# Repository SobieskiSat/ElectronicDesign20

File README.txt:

View this project on [CADLAB.io](https://cadlab.io/project/2295). 

Electronic design of the mainboard. more details TBA.

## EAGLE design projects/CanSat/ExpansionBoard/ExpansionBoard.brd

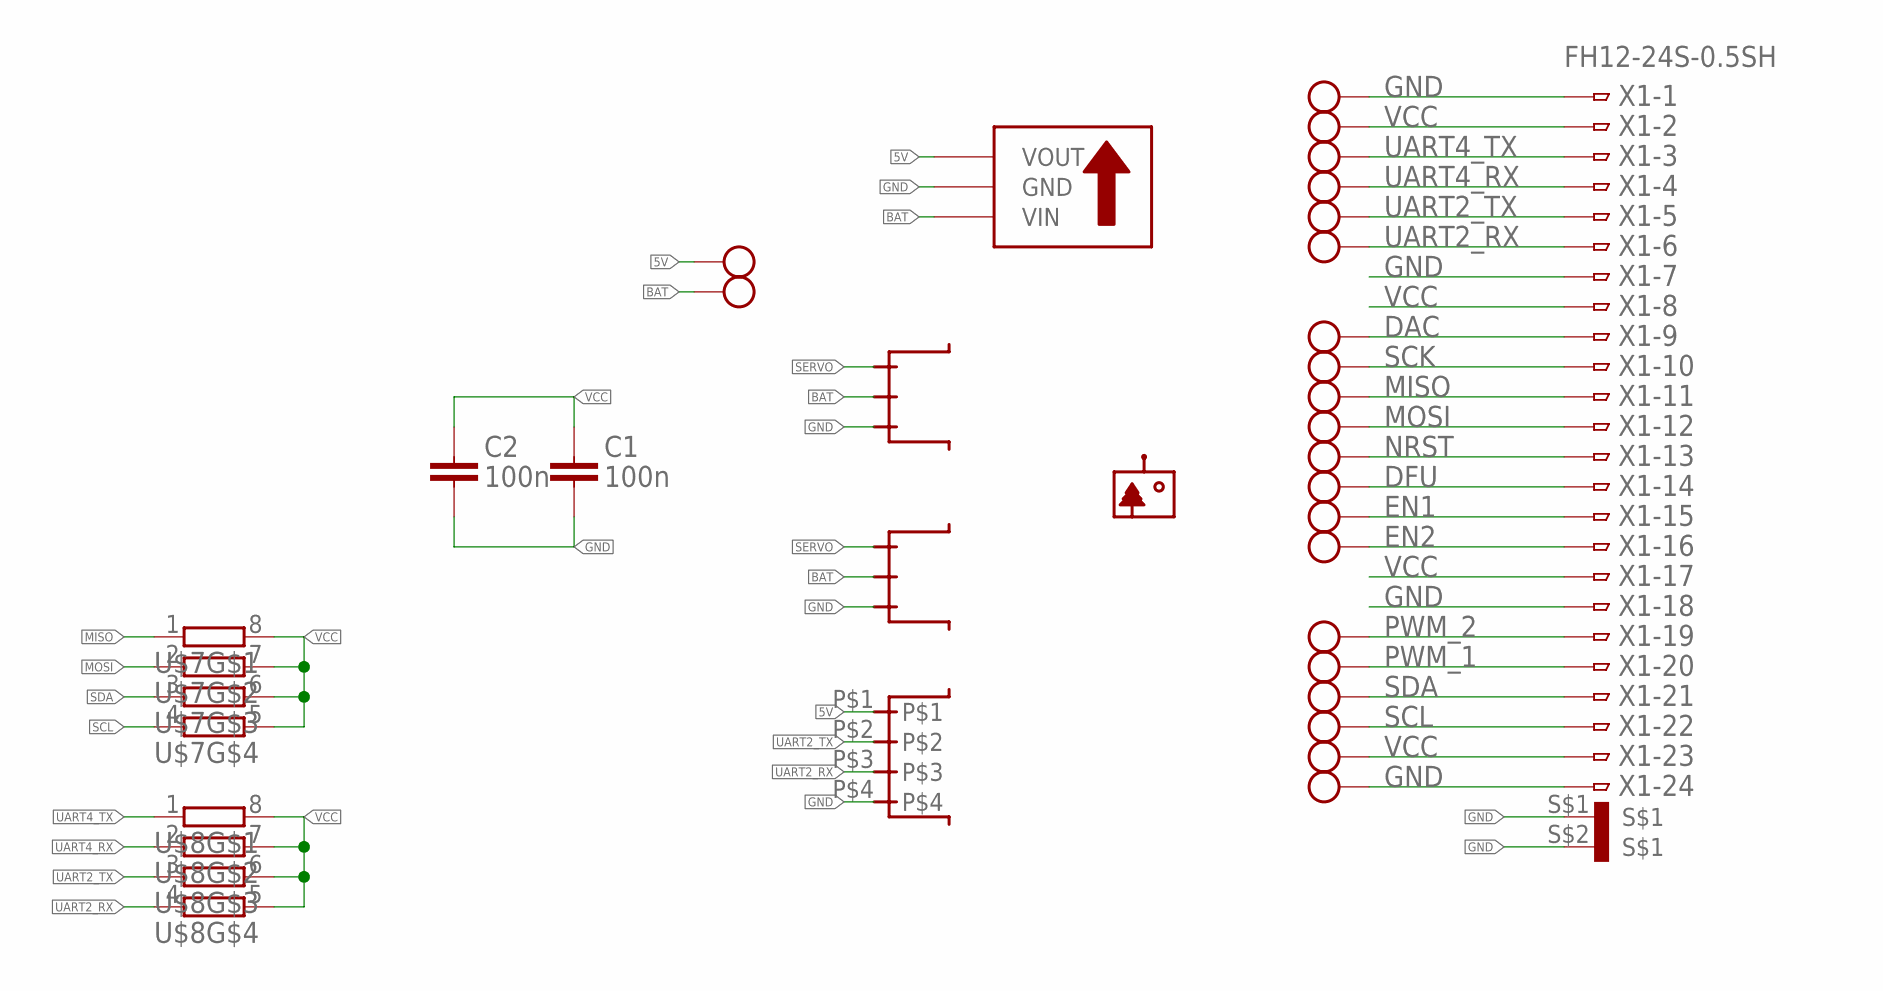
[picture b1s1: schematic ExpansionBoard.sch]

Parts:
C1, C2: 100n; C0603
U$1, U$23: THT_PADSQ; THT_PAD_SQ
U$2, U$3, U$4, U$5, U$6, U$9, U$10, U$11, U$12, U$13, U$14, U$15, U$16, U$19, U$20, U$21, U$22, U$24, U$27, U$30: THT_PAD
U$7, U$8: RESISTORARRAY; 0603-ARC
U$17: LOGOSQSM
U$25: MODULE_STEPUP
U$26: CONNECTOR_F_X4_JST_SMD; 4X_JSTSMD_F
U$28, U$29: CONNECTOR_F_X3_JST_SMD; 3X_JSTSMD_F
X1: FH12-24S-0.5SH

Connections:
5V: U$25.VOUT, U$26.P$1, U$27.P$1
BAT: U$25.VIN, U$28.P$2, U$29.P$2, U$30.P$1
DAC: U$9.P$1, X1.9 (1)
DFU: U$14.P$1, X1.14 (1)
EN1: U$15.P$1, X1.15 (1)
EN2: U$16.P$1, X1.16 (1)
GND: C1.2, C2.2, U$1.P$1, U$23.P$1, U$25.GND, U$26.P$4, U$28.P$3, U$29.P$3, X1.1, X1.7 (1), X1.18 (1), X1.24 (1), X1.S$1, X1.S$2
MISO: U$7.1, U$11.P$1, X1.11 (1)
MOSI: U$7.2 (1), U$12.P$1, X1.12 (1)
NRST: U$13.P$1, X1.13 (1)
PWM_1: U$20.P$1, X1.20 (1)
PWM_2: U$19.P$1, X1.19 (1)
SCK: U$10.P$1, X1.10 (1)
SCL: U$7.4 (1), U$22.P$1, X1.22 (1)
SDA: U$7.3 (1), U$21.P$1, X1.21 (1)
SERVO: U$28.P$1, U$29.P$1
UART2_RX: U$6.P$1, U$8.4 (1), U$26.P$3, X1.6 (1)
UART2_TX: U$5.P$1, U$8.3 (1), U$26.P$2, X1.5 (1)
UART4_RX: U$4.P$1, U$8.2 (1), X1.4 (1)
UART4_TX: U$3.P$1, U$8.1, X1.3 (1)
VCC: C1.1, C2.1, U$2.P$1, U$7.5 (2), U$7.6 (2), U$7.7 (2), U$7.8 (2), U$8.5 (2), U$8.6 (2), U$8.7 (2), U$8.8 (2), U$24.P$1, X1.2 (1), X1.8 (1), X1.17 (1), X1.23 (1)

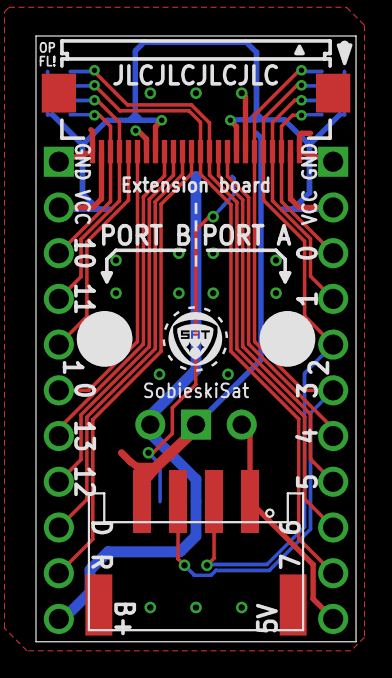
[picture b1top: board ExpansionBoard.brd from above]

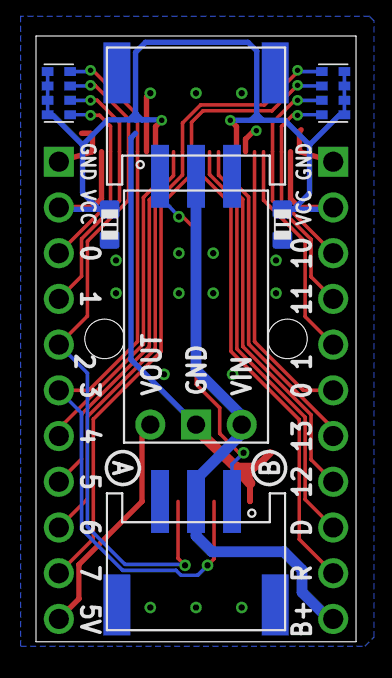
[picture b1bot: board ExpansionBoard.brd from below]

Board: 2 copper layers, 17.8 x 33.7 mm, 32 parts (7 on the bottom side), 21 nets.

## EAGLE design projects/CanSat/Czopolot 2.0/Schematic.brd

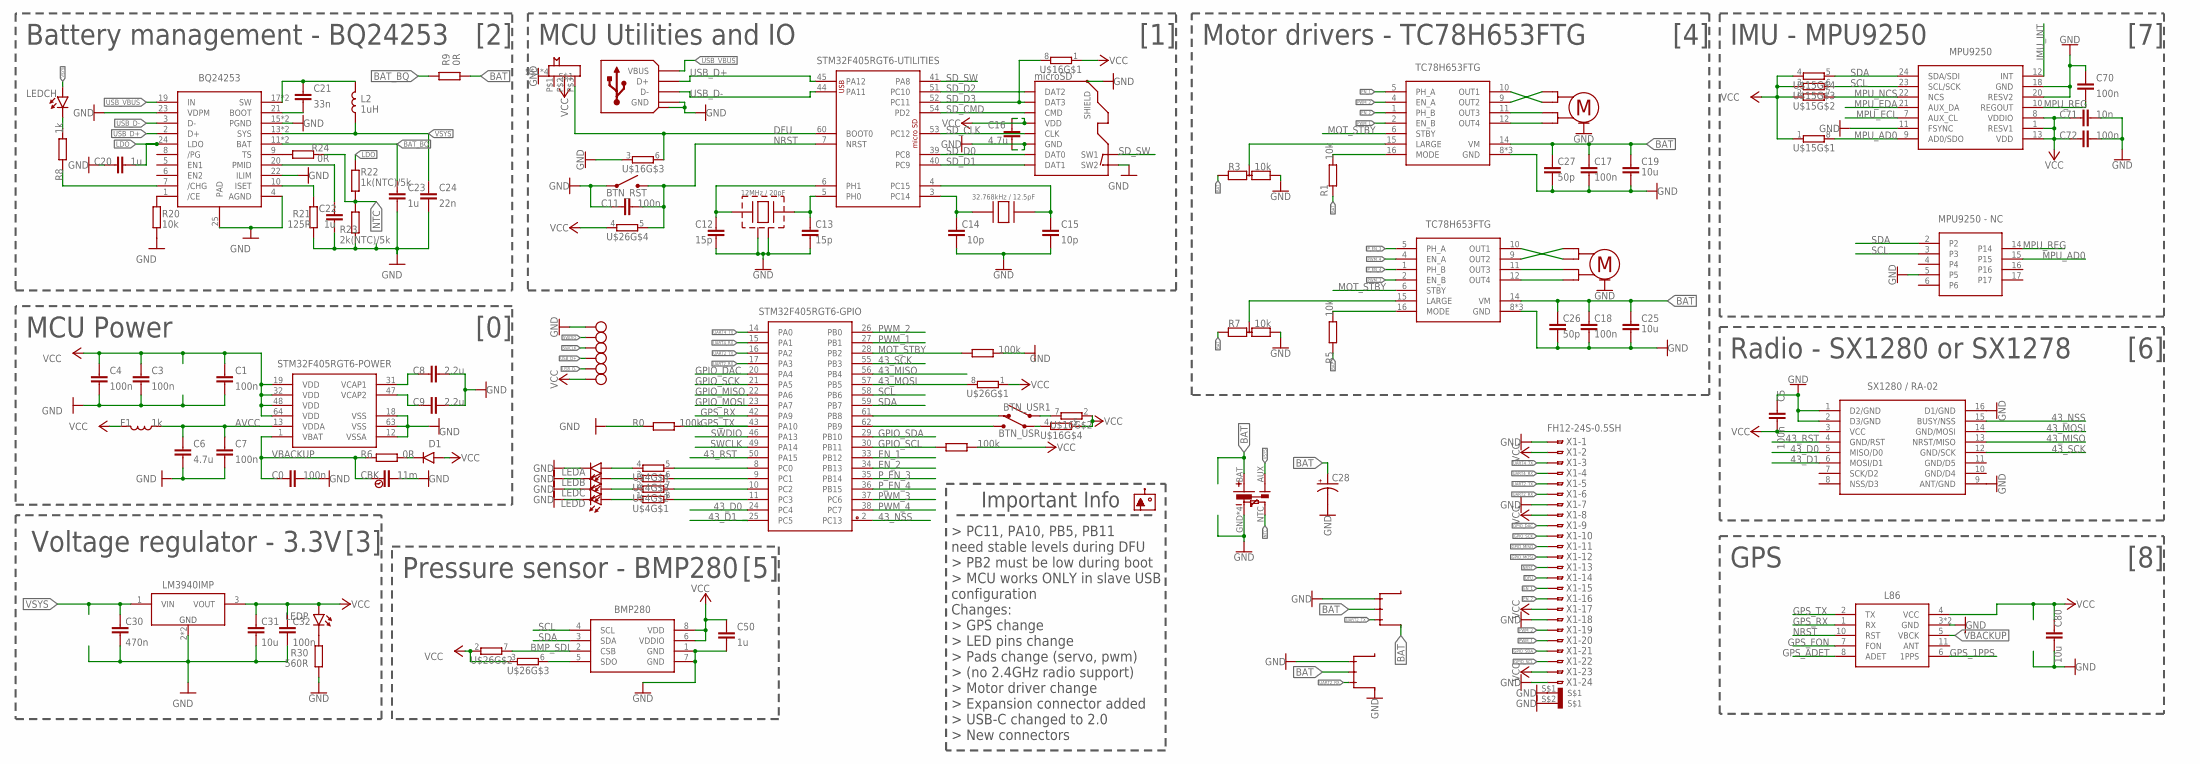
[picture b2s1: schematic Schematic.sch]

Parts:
BTN_DFU: SLIDE-SWITCH2; SLIDE-SWITCH-2
BTN_RST: PUSH-SWITCH; SWITCH_SMD
BTN_USR, BTN_USR1: PUSH-SWITCH; SWITCH_SMD
C0, C1, C3, C4, C5, C7, C11, C17, C18, C32, C70, C72: 100n; C0603
C6, C16: 4.7u; C0603
C8, C9: 2.2u; C0603
C12, C13: 15p; C0603
C14, C15: 10p; C0603
C19, C25, C31: 10u; C1206
C20, C22, C23, C50: 1u; C0603
C21: 33n; C0603
C24: 22n; C0603
C26, C27: 50p; C0603
C28: CPOL-US153CLV-0405; 153CLV-0405
C30: 470n; C0603
C71: 10n; C0603
C80: 10u; C0603
CBK: 11m; CPH3225A
D1: DIODE; R0603
F1: 1k; R0603
L2: 1uH; INDUCTOR_VISHAY
LEDA: LED0805; CHIPLED_0805
LEDB: LED0805; CHIPLED_0805
LEDC: LED0805; CHIPLED_0805
LEDCH: LED0805; CHIPLED_0805
LEDD: LED0805; CHIPLED_0805
LEDP: LED0805; CHIPLED_0805
LM3940IMP: REGULATOR; SOT230P700X180-4N
R0, R2, R4: 100k; R0603
R1, R5, R20: 10k; R0603
R3, R7: 10k; DR0603
R6, R9, R24: 0R; R0603
R8: 1k; R0603
R21: 125R; R0603
R22: 1k(NTC)/5k; R0603
R23: 2k(NTC)/5k; R0603
R30: 560R; R0603
U$1: STM32F405RGT6; QFP50P1200X1200X160-64N
U$2: MICROSD_HOLDER
U$3: L86
U$4, U$15, U$16, U$26: RESISTORARRAY; 0603-ARC
U$5: 32.768kHz / 12.5pF; OSC32X15
U$6: 12MHz / 20pF; OSCCC320X250X80N
U$7: USB2.0; USB-C(2)
U$8: BMP280
U$9: MPU9250USR; MPU9250
U$10: BQ24253; QFN50P400X400X100-25T270N
U$11, U$12: TC78H653FTG; QFN50P300X300X90-17T170N
U$13, U$17: MOTOR_DUO; 4(2)X_JSTSMD_F
U$14: BAT_JST_4(3); 4(3)X_JSTSMD_F
U$18: LOGOSQSM
U$19, U$20: CONNECTOR_F_X3_JST_SMD; 3X_JSTSMD_F
U$21: LORADUO; MODULE_SX1280
U$25: GPIO_DEBUG
X1: FH12-24S-0.5SH

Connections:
43_D0: U$1.24 (PC4), U$21.5 (MISO/D0)
43_D1: U$1.25 (PC5), U$21.6 (MOSI/D1)
43_MISO: U$1.56 (PB4), U$21.13 (NRST/MISO)
43_MOSI: U$1.57 (PB5), U$21.14 (GND/MOSI), U$26.8 (2)
43_NSS: U$1.2 (PC13), U$21.15 (BUSY/NSS)
43_RST: U$1.50 (PA15), U$21.4 (GND/RST)
43_SCK: U$1.55 (PB3), U$21.12 (GND/SCK)
AVCC: C6.1, C7.1, F1.2, U$1.13 (VDDA)
BAT: C17.1, C18.1, C19.1, C25.1, C26.1, C27.1, C28.+, R1.1, R3.2, R5.1, R7.2, R9.1, U$11.14 (VM), U$12.14 (VM), U$14.BAT (+), U$19.P$2, U$19.S$1, U$19.S$2, U$20.P$2
BAT_BQ: C23.1, R9.2, U$10.11 (BAT), U$10.12 (BAT)
BMP_SDI: U$8.2 (CSB), U$26.7 (2)
BMP_SDO: U$8.5 (SDO), U$26.6 (2)
DFU: BTN_DFU.P$3, U$1.60 (BOOT0), U$16.6 (2), X1.14 (1)
EN_1: U$1.33 (PB12), U$12.5 (PH_A), X1.15 (1)
EN_2: U$1.34 (PB13), U$12.1 (PH_B), X1.16 (1)
GND: BTN_DFU.S$1, BTN_DFU.S$2, BTN_DFU.S$3, BTN_DFU.S$4, BTN_RST.P$1, BTN_RST.P$4, C0.2, C1.2, C3.2, C4.2, C5.1, C6.2, C7.2, C8.2, C9.2, C11.1, C12.2, C13.2, C14.2, C15.2, C16.1, C17.2, C18.2, C19.2, C20.1, C22.2, C23.2, C24.2, C25.2, C26.2, C27.2, C28.-, C30.2, C31.2, C32.2, C50.2, C70.1, C71.2, C72.2, C80.2, CBK.P$2 (2), LEDA.C, LEDB.C, LEDC.C, LEDD.C, LM3940IMP.2 (GND), LM3940IMP.4 (GND), R0.1, R2.1, R3.3, R7.3, R20.1, R21.1, R23.1, R30.2, U$1.12 (VSSA), U$1.18 (VSS), U$1.63 (VSS), U$2.GND, U$2.SHIELD@1 (SHIELD), U$2.SHIELD@2 (SHIELD), U$2.SHIELD@3 (SHIELD), U$2.SHIELD@4 (SHIELD), U$2.SW2, U$3.3 (GND), U$3.12 (GND), U$6.2 (GND), U$6.4 (GND), U$7.A1 (GND), U$7.A12 (GND), U$7.B1 (GND), U$7.B12 (GND), U$7.MID@1 (SHIELD), U$7.MID@2 (SHIELD), U$7.S$1 (GND), U$7.S$2 (GND), U$7.S$3 (GND), U$7.S$4 (GND), U$7.S$5 (GND), U$7.S$6 (GND), U$7.S$7 (GND), U$7.S$8 (GND), U$8.1 (GND), U$8.7 (GND), U$9.5, U$9.11 (FSYNC), U$9.18 (GND), U$9.20 (RESV2), U$10.4 (AGND), U$10.15 (PGND), U$10.16 (PGND), U$10.22 (ILIM), U$10.23 (VDPM), U$10.25 (PAD), U$11.8 (GND), U$11.13 (GND), U$11.17 (GND), U$12.8 (GND), U$12.13 (GND), U$12.17 (GND), U$13.S$1, U$13.S$2, U$13.S$3, U$13.S$4, U$14.GND (-), U$14.S$1 (-), U$14.S$2 (-), U$14.S$3 (-), U$16.3 (1), U$17.S$1, U$17.S$2, U$17.S$3, U$17.S$4, U$19.P$1, U$20.P$1, U$20.S$1, U$20.S$2, U$21.1 (D2/GND), U$21.2 (D3/GND), U$21.9 (ANT/GND), U$21.16 (D1/GND), U$25.P$1, X1.1, X1.7 (1), X1.18 (1), X1.24 (1), X1.S$1, X1.S$2
GPIO_DAC: U$1.20 (PA4), X1.9 (1)
GPIO_MISO: U$1.22 (PA6), X1.11 (1)
GPIO_MOSI: U$1.23 (PA7), X1.12 (1)
GPIO_SCK: U$1.21 (PA5), X1.10 (1)
GPIO_SCL: R4.2, U$1.30 (PB11), X1.22 (1)
GPIO_SDA: U$1.29 (PB10), X1.21 (1)
GPS_1PPS: U$3.6 (1PPS)
GPS_ADET: U$3.8 (ADET)
GPS_FON: U$3.7 (FON)
GPS_RX: U$1.42 (PA9), U$3.1 (RX)
GPS_TX: R0.2, U$1.43 (PA10), U$3.2 (TX)
IMU_INT: U$9.12 (INT)
LDO: C20.2, R22.2, U$10.24 (LDO)
MOT_STBY: R2.2, U$1.28 (PB2), U$11.6 (STBY), U$12.6 (STBY)
MPU_AD0: U$9.9 (AD0/SDO), U$9.15, U$15.8 (2)
MPU_ECL: U$9.7 (AUX_CL)
MPU_EDA: U$9.21 (AUX_DA)
MPU_NCS: U$9.22 (NCS), U$15.7 (2)
MPU_REG: C70.2, U$9.10 (REGOUT), U$9.14
unnamed: LEDD.A, U$4.1
unnamed: LEDC.A, U$4.2 (1)
unnamed: LEDCH.C, R8.2
unnamed: U$11.9 (OUT2), U$13.P$1
unnamed: BTN_USR.P$2, BTN_USR.P$3, U$1.62 (PB9)
unnamed: C21.2, U$10.21 (BOOT)
unnamed: BTN_USR.P$1, BTN_USR.P$4, U$16.4 (1)
unnamed: C9.1, U$1.47 (VCAP2)
unnamed: C8.1, U$1.31 (VCAP1)
unnamed: R8.1, U$10.7 (/CHG)
unnamed: C12.1, U$1.6 (PH1), U$6.1
unnamed: C13.1, U$1.5 (PH0), U$6.3
unnamed: C14.1, U$1.3 (PC14), U$5.P$1
unnamed: C15.1, U$1.4 (PC15), U$5.P$2
unnamed: U$1.8 (PC0), U$4.5 (2)
unnamed: R24.2, U$10.9 (TS)
unnamed: R21.2, U$10.10 (ISET)
unnamed: U$1.11 (PC3), U$4.8 (2)
unnamed: U$1.10 (PC2), U$4.7 (2)
unnamed: C21.1, L2.P$1, U$10.17 (SW), U$10.18 (SW)
unnamed: LEDP.C, R30.1
unnamed: U$11.10 (OUT1), U$13.P$2
unnamed: C22.1, U$10.20 (PMID)
unnamed: BTN_USR1.P$1, BTN_USR1.P$4, U$16.7 (2)
unnamed: U$1.9 (PC1), U$4.6 (2)
unnamed: R20.2, U$10.1 (/CE)
unnamed: BTN_USR1.P$2, BTN_USR1.P$3, U$1.61 (PB8)
unnamed: U$11.11 (OUT3), U$13.P$3
unnamed: U$11.12 (OUT4), U$13.P$4
unnamed: U$12.9 (OUT2), U$17.P$1
unnamed: U$12.10 (OUT1), U$17.P$2
unnamed: U$12.11 (OUT3), U$17.P$3
unnamed: U$12.12 (OUT4), U$17.P$4
unnamed: R1.2, U$12.16 (MODE)
unnamed: LEDB.A, U$4.3 (1)
unnamed: LEDA.A, U$4.4 (1)
unnamed: R3.1, U$12.15 (LARGE)
unnamed: R5.2, U$11.16 (MODE)
unnamed: D1.2, R6.2
unnamed: R7.1, U$11.15 (LARGE)
NRST: BTN_RST.P$2, BTN_RST.P$3, C11.2, U$1.7 (NRST), U$3.10 (RST), U$26.5 (2), X1.13 (1)
NTC: R22.1, R23.2, R24.1, U$14.NTC
PWM_1: U$1.27 (PB1), U$12.2 (EN_B), X1.20 (1)
PWM_2: U$1.26 (PB0), U$12.4 (EN_A), X1.19 (1)
PWM_3: U$1.37 (PC6), U$11.2 (EN_B)
PWM_4: U$1.38 (PC7), U$11.4 (EN_A)
P_EN_3: U$1.35 (PB14), U$11.5 (PH_A)
P_EN_4: U$1.36 (PB15), U$11.1 (PH_B)
SCL: U$1.58 (PB6), U$8.4 (SCL), U$9.3, U$9.23 (SCL/SCK), U$15.6 (2)
SDA: U$1.59 (PB7), U$8.3 (SDA), U$9.2, U$9.24 (SDA/SDI), U$15.5 (2)
SD_CLK: U$1.53 (PC12), U$2.CLK
SD_CMD: U$1.54 (PD2), U$2.CMD
SD_D0: U$1.39 (PC8), U$2.D0 (DAT0)
SD_D1: U$1.40 (PC9), U$2.D1 (DAT1)
SD_D2: U$1.51 (PC10), U$2.D2 (DAT2)
SD_D3: U$1.52 (PC11), U$2.D3 (DAT3), U$16.8 (2)
SD_SW: U$1.41 (PA8), U$2.SW1
SWCLK: U$1.49 (PA14), U$25.P$3
SWDIO: U$1.46 (PA13), U$25.P$2
UART2_RX: U$1.17 (PA3), U$20.P$3, X1.6 (1)
UART2_TX: U$1.16 (PA2), U$19.P$3, X1.5 (1)
UART4_RX: U$1.15 (PA1), X1.4 (1)
UART4_TX: U$1.14 (PA0), X1.3 (1)
USB_D+: U$1.45 (PA12), U$7.A6 (D+), U$7.B6 (D+), U$10.2 (D+), U$25.P$4
USB_D-: U$1.44 (PA11), U$7.A7 (D-), U$7.B7 (D-), U$10.3 (D-), U$25.P$5
USB_VBUS: U$7.A4 (VBUS), U$7.A9 (VBUS), U$7.B4 (VBUS), U$7.B9 (VBUS), U$10.19 (IN)
VBACKUP: C0.1, CBK.P$1 (1), R6.1, U$1.1 (VBAT), U$3.5 (VBCK)
VCC: BTN_DFU.P$2, C1.1, C3.1, C4.1, C5.2, C16.2, C31.1, C32.1, C50.1, C71.1, C72.1, C80.1, D1.1, F1.1, LEDP.A, LM3940IMP.3 (VOUT), R4.1, U$1.19 (VDD), U$1.32 (VDD), U$1.48 (VDD), U$1.64 (VDD), U$2.VCC (VDD), U$3.4 (VCC), U$8.6 (VDDIO), U$8.8 (VDD), U$9.1 (RESV1), U$9.8 (VDDIO), U$9.13 (VDD), U$15.1, U$15.2 (1), U$15.3 (1), U$15.4 (1), U$16.1, U$16.2 (1), U$16.5 (2), U$21.3 (VCC), U$25.P$6, U$26.1, U$26.2 (1), U$26.3 (1), U$26.4 (1), X1.2 (1), X1.8 (1), X1.17 (1), X1.23 (1)
VSYS: C24.1, C30.1, L2.P$2, LEDCH.A, LM3940IMP.1 (VIN), U$10.13 (SYS), U$10.14 (SYS), U$14.AUX (AUX+)

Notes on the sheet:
GPS
Pressure sensor - BMP280
IMU - MPU9250
Radio - SX1280 or SX1278
Battery management - BQ24253
Voltage regulator - 3.3V
MCU Power
MCU Utilities and IO
Important Info
Motor drivers - TC78H653FTG
[0]
[1]
[2]
[3]
[4]
[5]
[6]
[7]
[8]
Changes: > GPS change > LED pins change > Pads change (servo, pwm) > (no 2.4GHz radio support) > Motor driver change > Expansion connector added > USB-C changed to 2.0 > New connectors

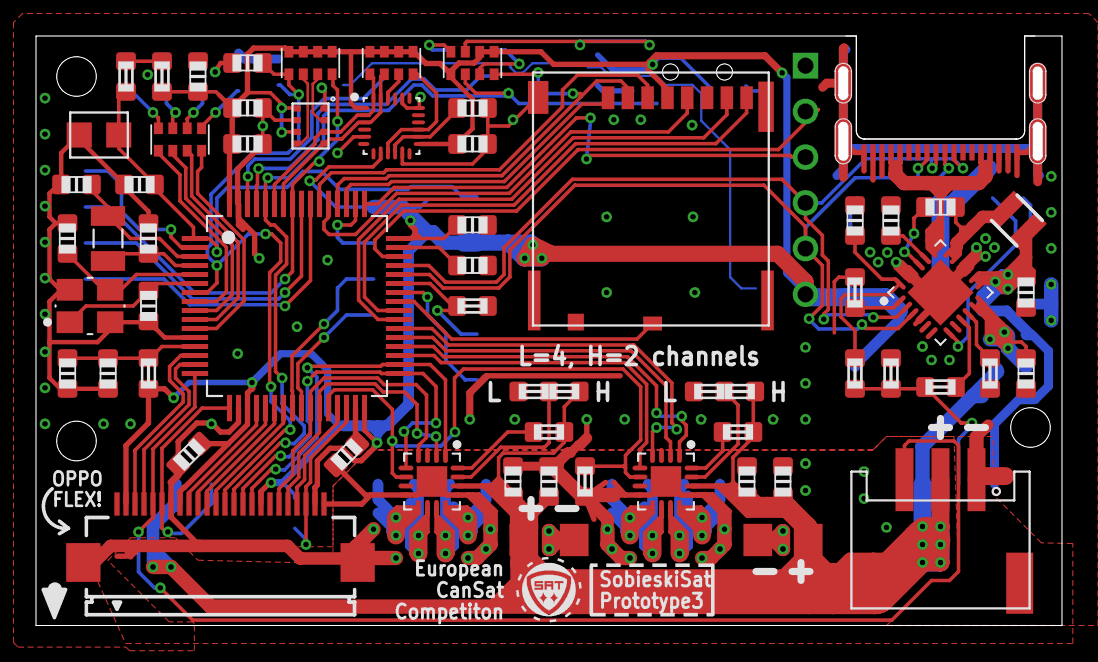
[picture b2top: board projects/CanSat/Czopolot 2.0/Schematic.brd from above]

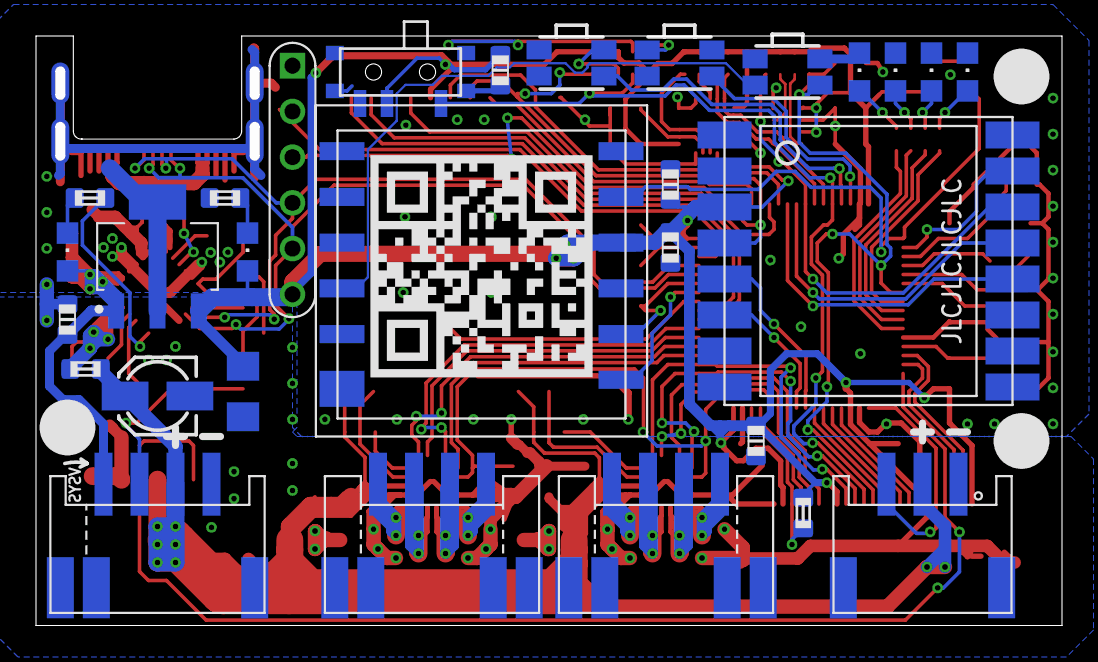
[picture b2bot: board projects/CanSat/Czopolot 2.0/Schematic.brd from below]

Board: 2 copper layers, 57.0 x 32.8 mm, 90 parts (29 on the bottom side), 98 nets.

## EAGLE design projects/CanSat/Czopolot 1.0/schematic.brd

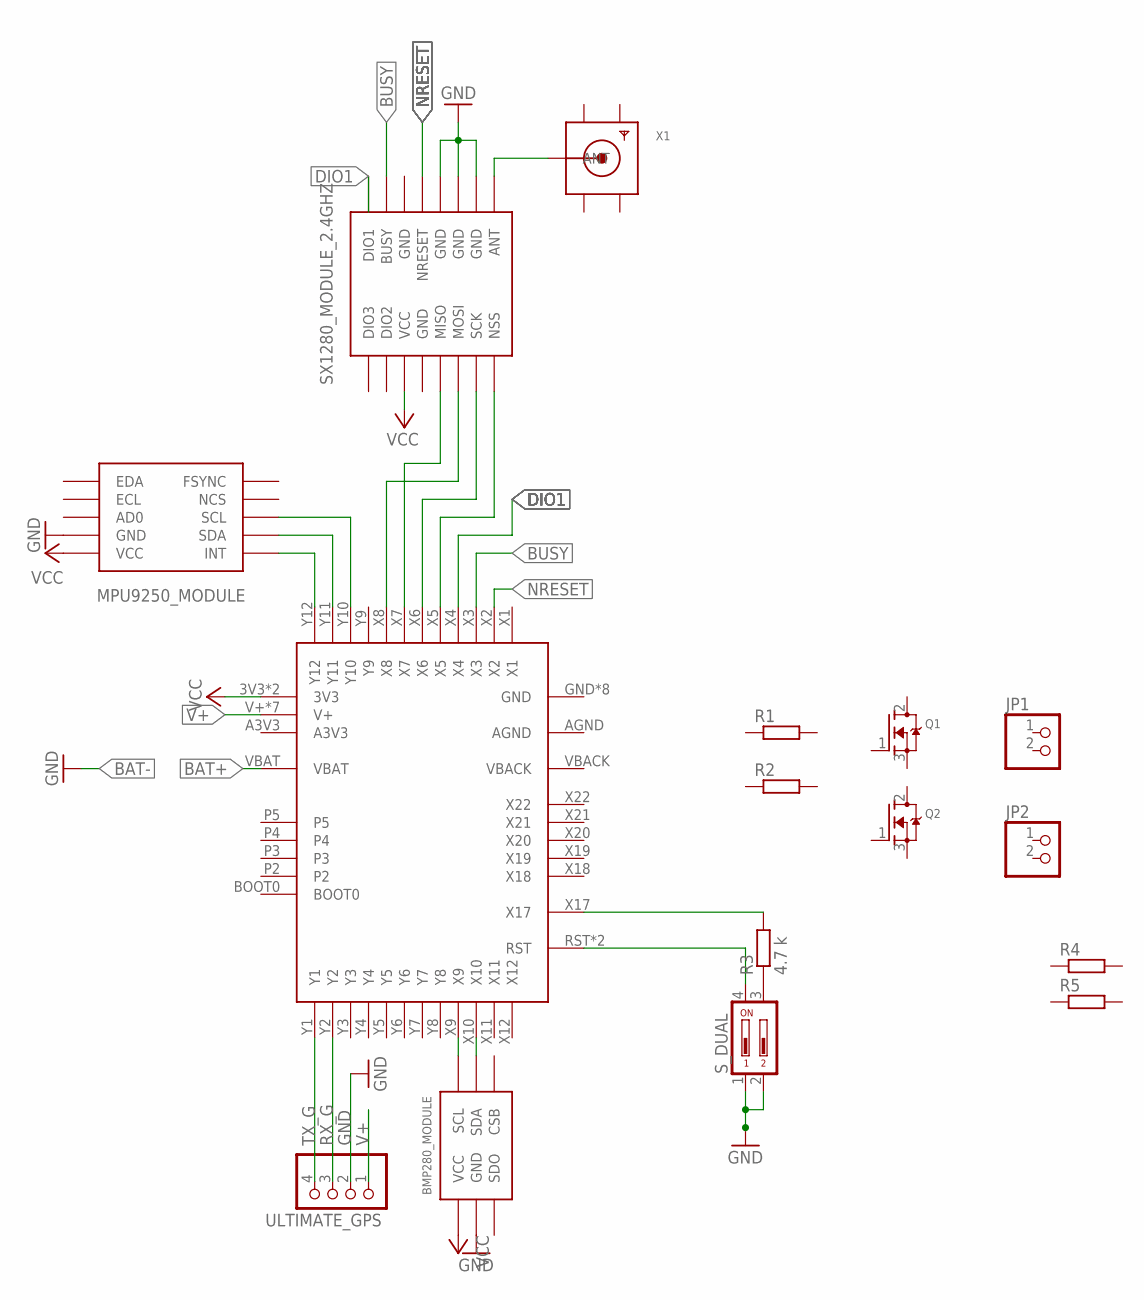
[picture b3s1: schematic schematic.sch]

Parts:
JP1, JP2: PINHD-1X2; 1X02
Q1, Q2: MOSFET-NGDS_TO220V; TO220V
R1, R2, R4: R-EU_0204/7; 0204/7
R3: 4.7 k; 0204/7
R5: R-EU_0207/10; 0207/10
U$1: PYBOARD1.1; MODULE_PYBOARD
U$3: MPU9250; MODULE_MPU9250
U$4: BMP280; MODULE_BMP280
U$5: SWITCH_DUAL
U$6: SX1280_2.4GHZ; MODULE_SX1280_THT
ULTIMATE_GPS: PINHD-1X4; 1X04
X1: SMACONNECTOR; SMA_DIP

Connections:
BAT+: U$1.VBAT
BUSY: U$1.X3, U$6.BUSY
DIO1: U$1.X4
GND: U$3.GND, U$4.GND, U$5.1, U$5.2, U$6.GND@3 (GND), U$6.GND@4 (GND), U$6.GND@5 (GND), ULTIMATE_GPS.2
GND1: X1.GND1
GND2: X1.GND2
GND3: X1.GND3
GND4: X1.GND4
unnamed: U$1.X5, U$6.NSS
unnamed: U$1.X6, U$6.SCK
unnamed: U$1.X8, U$6.MOSI
unnamed: U$1.X7, U$6.MISO
unnamed: U$6.ANT, X1.ANTENNA (ANT)
unnamed: R3.1, U$5.3
unnamed: U$1.Y11, U$3.SDA
unnamed: U$1.Y10, U$3.SCL
unnamed: U$1.Y12, U$3.INT
unnamed: U$1.X9, U$4.SCL
unnamed: U$1.X10, U$4.SDA
unnamed: U$1.RST, U$1.RST1 (RST), U$5.4
unnamed: R3.2, U$1.X17
NRESET: U$1.X2, U$6.NRESET
RX_G: U$1.Y2, ULTIMATE_GPS.3
TX_G: U$1.Y1, ULTIMATE_GPS.4
V+: U$1.V+, U$1.V+1 (V+), U$1.V+2 (V+), U$1.V+3 (V+), U$1.V+4 (V+), U$1.V+5 (V+), U$1.V+6 (V+), ULTIMATE_GPS.1
VCC: U$1.3V3, U$1.3V3-1 (3V3), U$3.VCC, U$4.VCC, U$6.VCC

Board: 2 copper layers, 16 parts (0 on the bottom side), 20 nets, no tracks yet.

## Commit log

2019-11-17 Backlink to CADLAB.io has been added.
2019-11-18 File upload
2019-11-18 File separation
2019-11-18 null
2019-11-18 Add README.txt
2019-11-18 File update
2019-11-25 Work work..
2019-11-26 Work work...
2019-12-01 Work work.....
2019-12-04 updatejs
    pyboard
2019-12-04 Gitignore update
2019-12-05 Routing & placing ver.1
    Proposed routing for board.
    > Everyting seems optimal so far except for:
    > BMP280 (?move to the right)
2019-12-07 Schrinking...
2019-12-08 Oh God that's small..
2019-12-09 USB-C update
2019-12-09 Updated USB-C
2019-12-09 Backup upload
2019-12-09 usb-c fix
2019-12-09 Proposed routing ver.2
2019-12-09 Jeezz it's tiny...
2019-12-10 Switch added
    Duel switch and resistor added
    Resistor type switched to another to match the grid
2019-12-10 Added GND to switch
2019-12-11 Work work
2019-12-12 Schematic changes
    BQ25606 replaced with 24270
    USB OTG replaced with USB
2019-12-12 updated charging solution
    Swapped BQ24270 for a newer BQ24253
2019-12-12 Updated charging solution for czopolot 2.0
    Schematic update
2019-12-13 change in ppm
    Damian co ty tam zmieniasz LDO na VIN???
2019-12-13 charging work
2019-12-15 Switched SX1280
2019-12-16 Finished version 0.1
    -Full routing
    -Bad footprints
2019-12-16 Motor driver added
2019-12-22 fusion sync
2019-12-28 Revert "Motor driver added"
    This reverts commit 75eb9b0d133b9a877f65968a5a8719895b875b89.
2019-12-28 Version 0.2
2019-12-29 Version 0.3
2019-12-29 Motor driver changed
2020-01-04 some 3D models added
2020-01-04 3D Models added
2020-01-04 Pheripherials added
2020-01-05 Version 0.4
2020-01-05 fusion link change
2020-01-05 charger, NTC, minro improements
2020-01-05 minor improvements
    SD generally
2020-01-06 minor changes
2020-01-06 fusion transfer
2020-01-06 Screwholes added
2020-01-06 fusion
2020-01-06 Version 0.5
    Pre-final component placement
2020-01-06 Round traces test
2020-01-07 Pads backup
2020-01-07 VERSION 1.0.0
2020-01-07 433MHz support added
2020-01-09 Schematic updated for CDR
2020-01-09 schematic arrangement
2020-01-15 Version 1.1
2020-01-15 Small update
2020-01-15 Revert "Small update"
    This reverts commit c373715e058d3e625b4769dc3f0669b20e7862ed.
2020-01-15 pre-order check
2020-01-15 Micro update
2020-01-16 changed slots for USBC to BIG HOLES
2020-01-16 minor changes + new gerber
2020-01-16 fusion update
2020-01-16 Schematic values updated
2020-01-18 Cleaning up repo
2020-01-18 Assembly document added
2020-03-08 New version work
2020-03-08 added 0R at TS pin of charger
2020-03-09 Before global ripup
2020-03-10 corona fajranto despacito
2020-03-26 Before driver change
2020-04-12 Microcontroller and sensors done...
2020-04-13 Dual motor connectors added
2020-06-25 V2 work...
2020-06-28 V2 almost done
2020-06-29 GND yet to fix
2020-07-02 Extension board
2020-07-03 Before ordering
2020-07-03 Ordered
